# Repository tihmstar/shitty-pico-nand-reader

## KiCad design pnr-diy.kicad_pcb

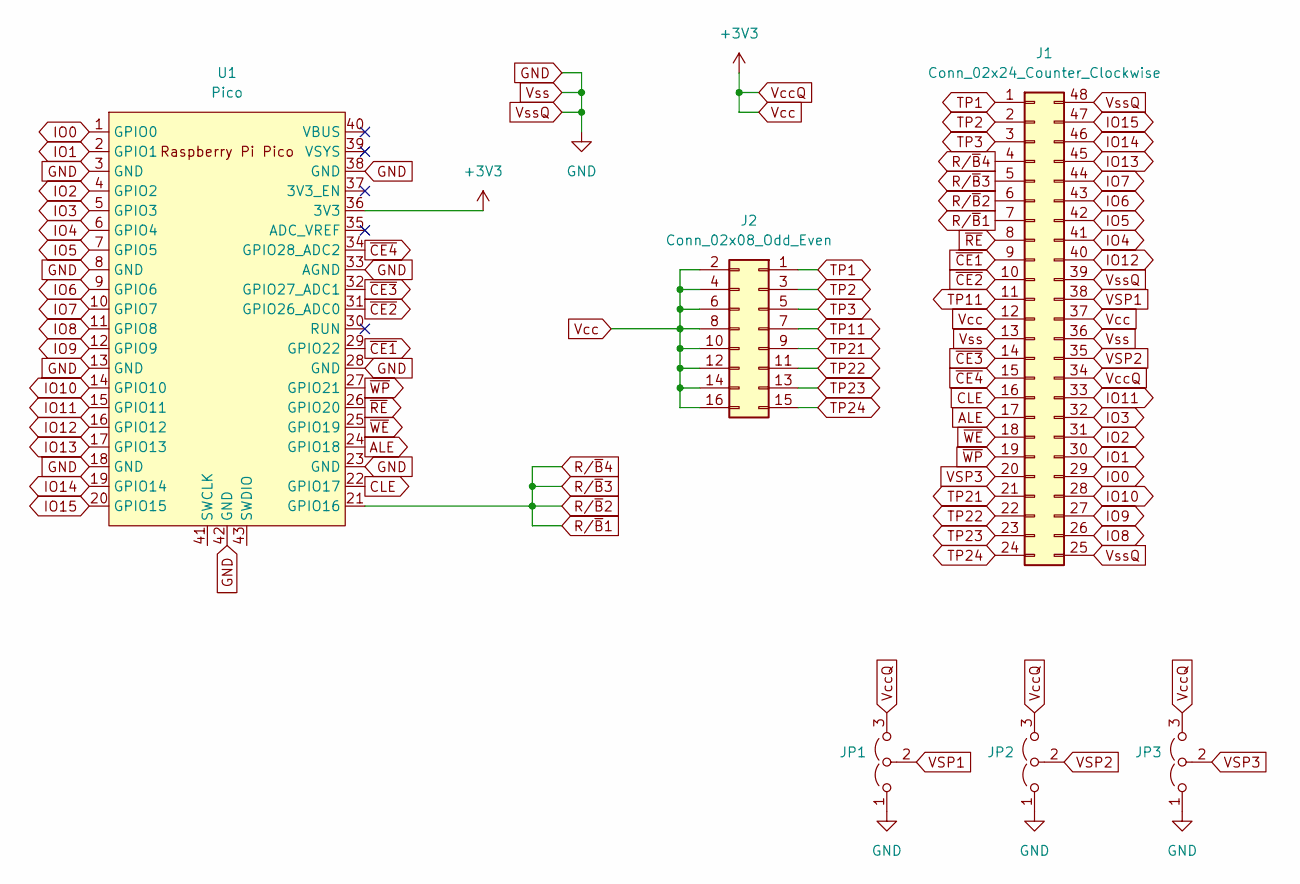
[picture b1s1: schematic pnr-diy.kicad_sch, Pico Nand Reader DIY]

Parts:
J1: Conn_02x24_Counter_Clockwise; DIP-48_W15.24mm
J2: Conn_02x08_Odd_Even; PinHeader_2x08_P2.54mm_Vertical
JP1, JP2, JP3: J_VSP1; PinHeader_1x03_P2.54mm_Vertical
U1: Pico; RPi_Pico_SMD_TH

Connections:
ALE: J1.17, U1.24 (GPIO18)
CLE: J1.16, U1.22 (GPIO17)
GND: J1.13, J1.25, J1.36, J1.39, J1.48, JP1.1 (A), JP2.1 (A), JP3.1 (A), U1.3 (GND), U1.8 (GND), U1.13 (GND), U1.18 (GND), U1.23 (GND), U1.28 (GND), U1.33 (AGND), U1.38 (GND), U1.42 (GND)
IO0: J1.29, U1.1 (GPIO0)
IO1: J1.30, U1.2 (GPIO1)
IO2: J1.31, U1.4 (GPIO2)
IO3: J1.32, U1.5 (GPIO3)
IO4: J1.41, U1.6 (GPIO4)
IO5: J1.42, U1.7 (GPIO5)
IO6: J1.43, U1.9 (GPIO6)
IO7: J1.44, U1.10 (GPIO7)
IO8: J1.26, U1.11 (GPIO8)
IO9: J1.27, U1.12 (GPIO9)
IO10: J1.28, U1.14 (GPIO10)
IO11: J1.33, U1.15 (GPIO11)
IO12: J1.40, U1.16 (GPIO12)
IO13: J1.45, U1.17 (GPIO13)
IO14: J1.46, U1.19 (GPIO14)
IO15: J1.47, U1.20 (GPIO15)
R/~B1: J1.4, J1.5, J1.6, J1.7, U1.21 (GPIO16)
TP1: J1.1, J2.1
TP2: J1.2, J2.3
TP3: J1.3, J2.5
TP11: J1.11, J2.7
TP21: J1.21, J2.9
TP22: J1.22, J2.11
TP23: J1.23, J2.13
TP24: J1.24, J2.15
VSP1: J1.38, JP1.2 (C)
VSP2: J1.35, JP2.2 (C)
VSP3: J1.20, JP3.2 (C)
Vcc: J1.12, J1.34, J1.37, J2.2, J2.4, J2.6, J2.8, J2.10, J2.12, J2.14, J2.16, JP1.3 (B), JP2.3 (B), JP3.3 (B), U1.36 (3V3)
~CE1: J1.9, U1.29 (GPIO22)
~CE2: J1.10, U1.31 (GPIO26_ADC0)
~CE3: J1.14, U1.32 (GPIO27_ADC1)
~CE4: J1.15, U1.34 (GPIO28_ADC2)
~RE: J1.8, U1.26 (GPIO20)
~WE: J1.18, U1.25 (GPIO19)
~WP: J1.19, U1.27 (GPIO21)

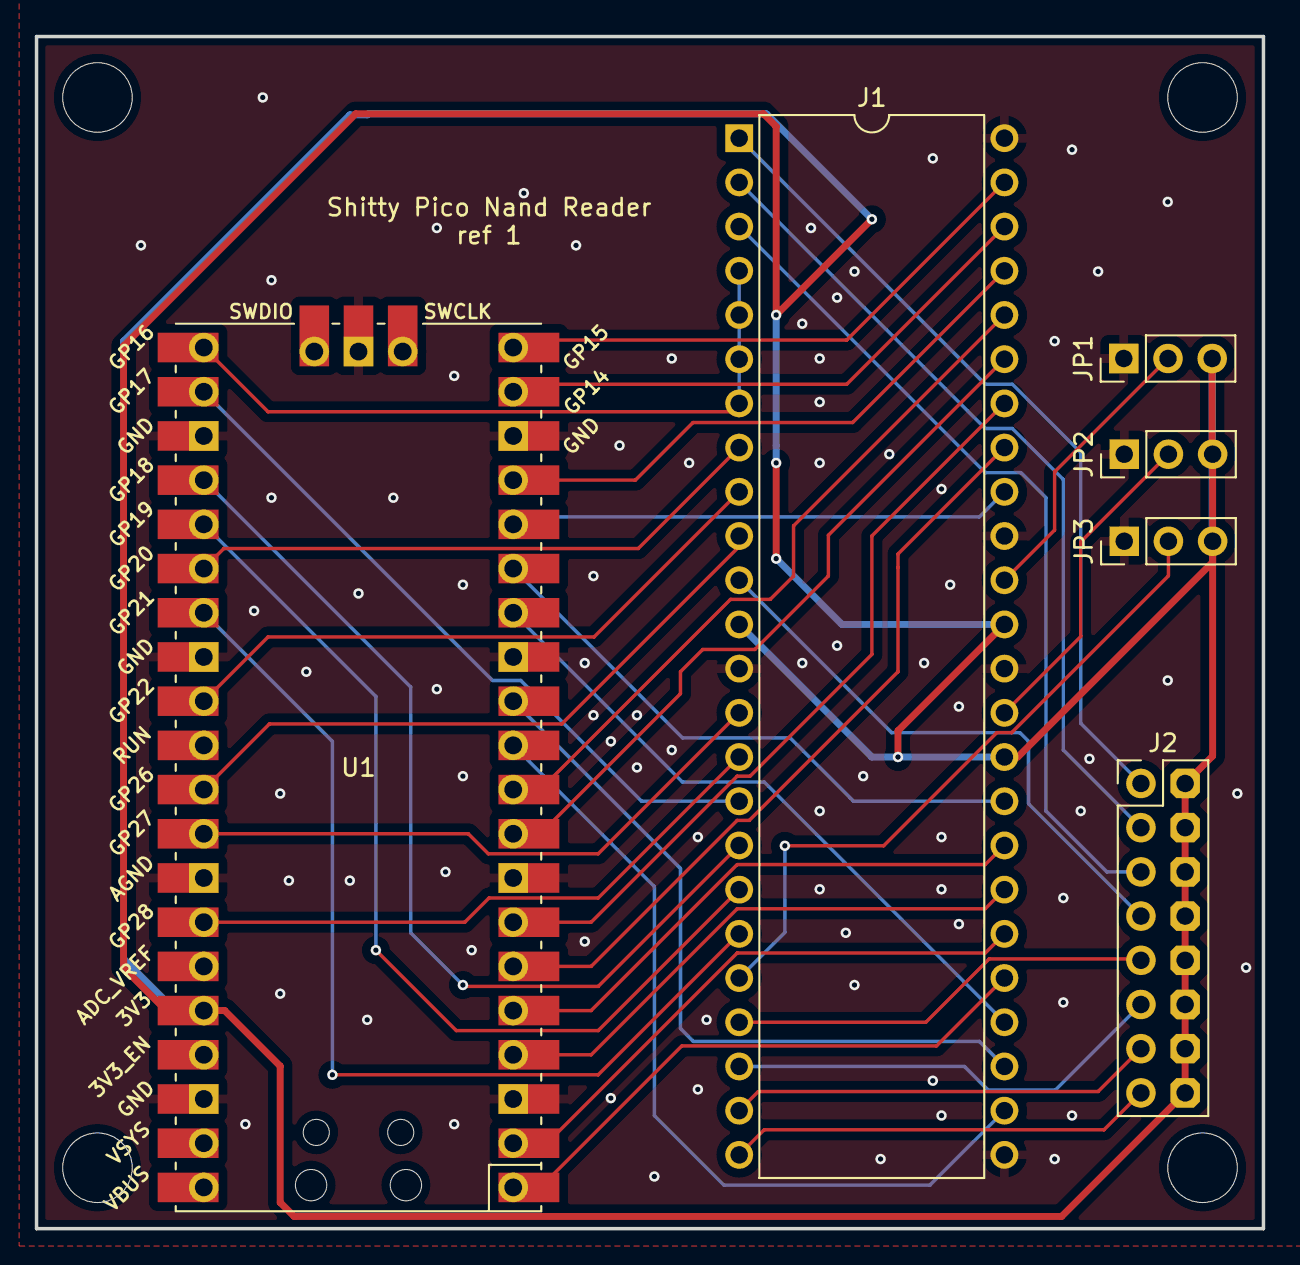
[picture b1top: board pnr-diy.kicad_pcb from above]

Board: 2 copper layers, 70.5 x 68.5 mm, 6 parts (0 on the bottom side), 39 nets.

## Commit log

2024-10-19 make holes bigger
